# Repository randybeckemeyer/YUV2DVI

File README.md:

# YUV2DVI
Component Video to DVI for Capture Cards

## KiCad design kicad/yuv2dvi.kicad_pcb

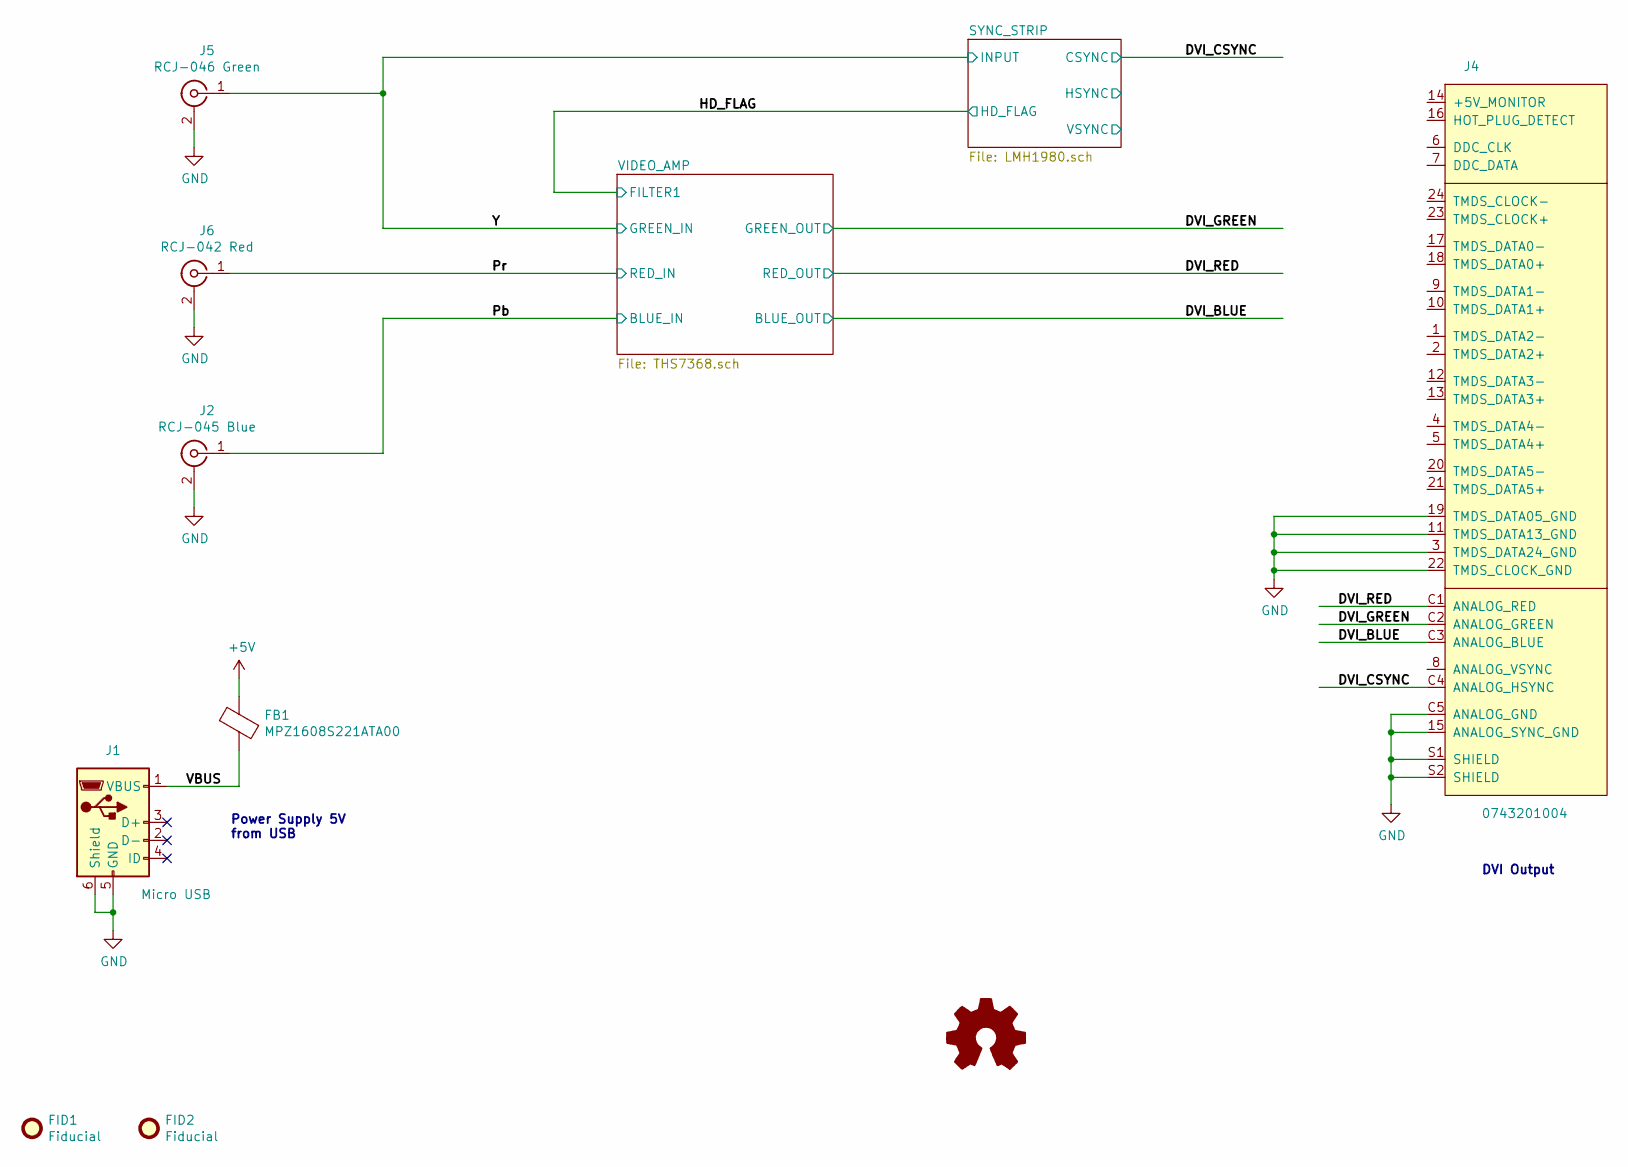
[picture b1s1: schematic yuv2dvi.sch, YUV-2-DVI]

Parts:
FB1: MPZ1608S221ATA00; L_0603_1608Metric_Pad1.05x0.95mm_HandSolder; MPN MPZ1608S221ATA00; Digikey 445-1565-1-ND
FID1, FID2: Fiducial; Fiducial_1mm_Mask2mm
J1: Micro USB; USB_Micro-B_Molex-105017-0001; MPN 1050170001; Digikey WM1399CT-ND
J2: RCJ-045 Blue; Connector-RCJ-045; MPN RCJ-045; Digikey CP-1422-ND
J4: 0743201004; Connector-DVI-0743201004; MPN 0743201004; Digikey WM5600-ND
J5: RCJ-046 Green; Connector-RCJ-046; MPN RCJ-046; Digikey CP-1423-ND
J6: RCJ-042 Red; Connector-RCJ-042; MPN RCJ-042; Digikey CP-1419-ND
LOGO1: Logo_Open_Hardware_Small; OSHW-Logo2_14.6x12mm_SilkScreen

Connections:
+5V: FB1.1; also elsewhere on the board
/DVI_BLUE: J4.C3 (ANALOG_BLUE); also elsewhere on the board
/DVI_CSYNC: J4.C4 (ANALOG_HSYNC); also elsewhere on the board
/DVI_GREEN: J4.C2 (ANALOG_GREEN); also elsewhere on the board
/DVI_RED: J4.C1 (ANALOG_RED); also elsewhere on the board
/Pb: J2.1 (In); also elsewhere on the board
/Pr: J6.1 (In); also elsewhere on the board
/VBUS: FB1.2, J1.1 (VBUS)
/Y: J5.1 (In); also elsewhere on the board
GND: J1.5 (GND), J1.6 (Shield), J2.2 (Ext), J4.3 (TMDS_DATA24_GND), J4.11 (TMDS_DATA13_GND), J4.15 (ANALOG_SYNC_GND), J4.19 (TMDS_DATA05_GND), J4.22 (TMDS_CLOCK_GND), J4.C5 (ANALOG_GND), J4.S1 (SHIELD), J4.S2 (SHIELD), J5.2 (Ext), J6.2 (Ext); also elsewhere on the board

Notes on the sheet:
Power Supply 5V from USB
DVI Output

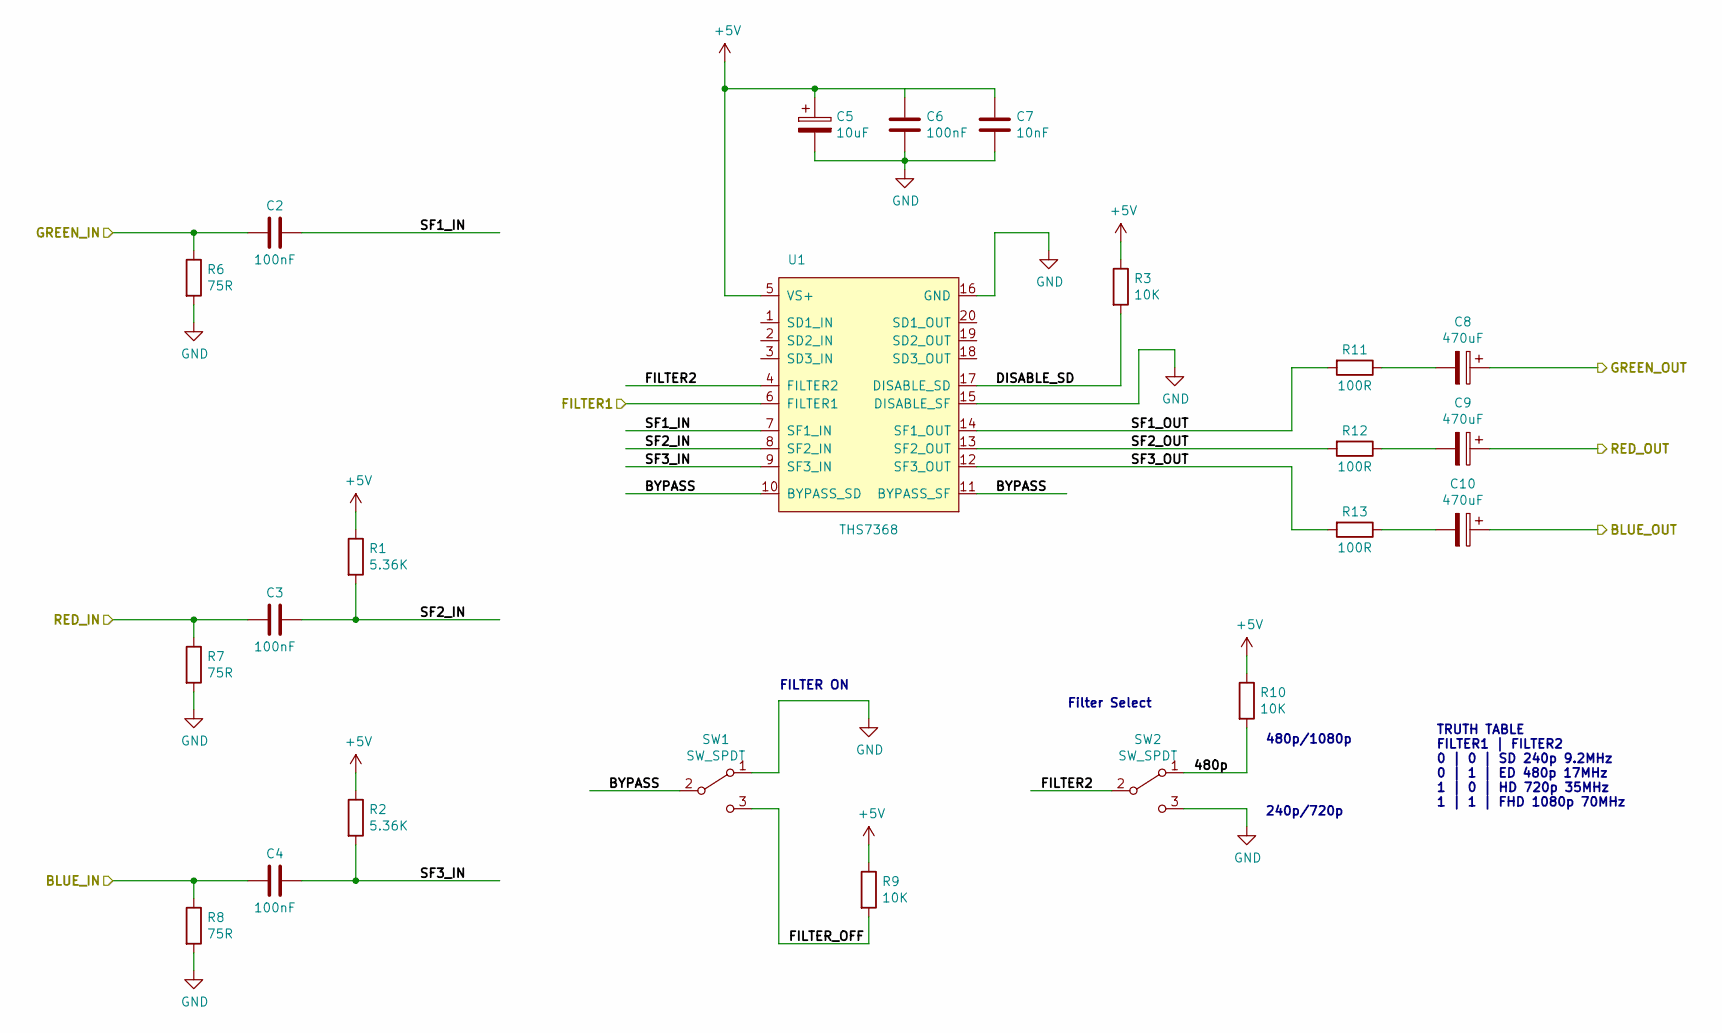
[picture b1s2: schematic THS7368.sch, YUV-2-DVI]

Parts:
C2, C3, C4, C6: 100nF; C_0603_1608Metric_Pad1.05x0.95mm_HandSolder; MPN CC0603KRX7R9BB104; Digikey 311-1344-1-ND
C5: 10uF; CP_EIA-3216-18_Kemet-A_Pad1.58x1.35mm_HandSolder; MPN TAJA106K016RNJ; Digikey 478-1655-1-ND
C7: 10nF; C_0603_1608Metric_Pad1.05x0.95mm_HandSolder; MPN CC0603KRX7R9BB103; Digikey 311-1085-1-ND
C8, C9, C10: 470uF; CP_Elec_8x10.5; MPN EEE-HA1A471UP; Digikey PCE4178CT-ND
R1, R2: 5.36K; R_0603_1608Metric_Pad1.05x0.95mm_HandSolder; MPN RC0603FR-075K36L; Digikey 311-5.36KHRCT-ND
R3, R9, R10: 10K; R_0603_1608Metric_Pad1.05x0.95mm_HandSolder; MPN RC0603FR-0710KL; Digikey 311-10.0KHRCT-ND
R6, R7, R8: 75R; R_0603_1608Metric_Pad1.05x0.95mm_HandSolder; MPN RC0603FR-0775RL; Digikey 311-75.0HRCT-ND
R11, R12, R13: 100R; R_0603_1608Metric_Pad1.05x0.95mm_HandSolder; MPN RC0603FR-07100RL; Digikey 311-100HRCT-ND
SW1, SW2: SW_SPDT; SW_NKK_GW12RCV; MPN GW12RCV; Digikey 360-3430-ND
U1: THS7368; TSSOP-20_4.4x6.5mm_P0.65mm; MPN THS7368IPWR; Digikey 296-25625-1-ND

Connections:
+5V: C5.1, C6.1, C7.1, R1.1, R2.1, R3.1, R9.1, R10.1, U1.5 (VS+); also elsewhere on the board
/DVI_BLUE: C10.1; also elsewhere on the board
/DVI_GREEN: C8.1; also elsewhere on the board
/DVI_RED: C9.1; also elsewhere on the board
/HD_FLAG: U1.6 (FILTER1); also elsewhere on the board
/Pb: C4.2, R8.1; also elsewhere on the board
/Pr: C3.2, R7.1; also elsewhere on the board
/VIDEO_AMP/480p: R10.2, SW2.1 (A)
/VIDEO_AMP/BYPASS: SW1.2 (B), U1.10 (BYPASS_SD), U1.11 (BYPASS_SF)
/VIDEO_AMP/DISABLE_SD: R3.2, U1.17 (DISABLE_SD)
/VIDEO_AMP/FILTER2: SW2.2 (B), U1.4 (FILTER2)
/VIDEO_AMP/FILTER_OFF: R9.2, SW1.3 (C)
/VIDEO_AMP/SF1_IN: C2.1, U1.7 (SF1_IN)
/VIDEO_AMP/SF1_OUT: R11.2, U1.14 (SF1_OUT)
/VIDEO_AMP/SF2_IN: C3.1, R1.2, U1.8 (SF2_IN)
/VIDEO_AMP/SF2_OUT: R12.2, U1.13 (SF2_OUT)
/VIDEO_AMP/SF3_IN: C4.1, R2.2, U1.9 (SF3_IN)
/VIDEO_AMP/SF3_OUT: R13.2, U1.12 (SF3_OUT)
/Y: C2.2, R6.1; also elsewhere on the board
GND: C5.2, C6.2, C7.2, R6.2, R7.2, R8.2, SW1.1 (A), SW2.3 (C), U1.15 (DISABLE_SF), U1.16 (GND); also elsewhere on the board
unnamed: C8.2, R11.1
unnamed: C9.2, R12.1
unnamed: C10.2, R13.1

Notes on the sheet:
FILTER ON
TRUTH TABLE FILTER1 | FILTER2 0 | 0 | SD 240p 9.2MHz 0 | 1 | ED 480p 17MHz 1 | 0 | HD 720p 35MHz 1 | 1 | FHD 1080p 70MHz
Filter Select
240p/720p
480p/1080p

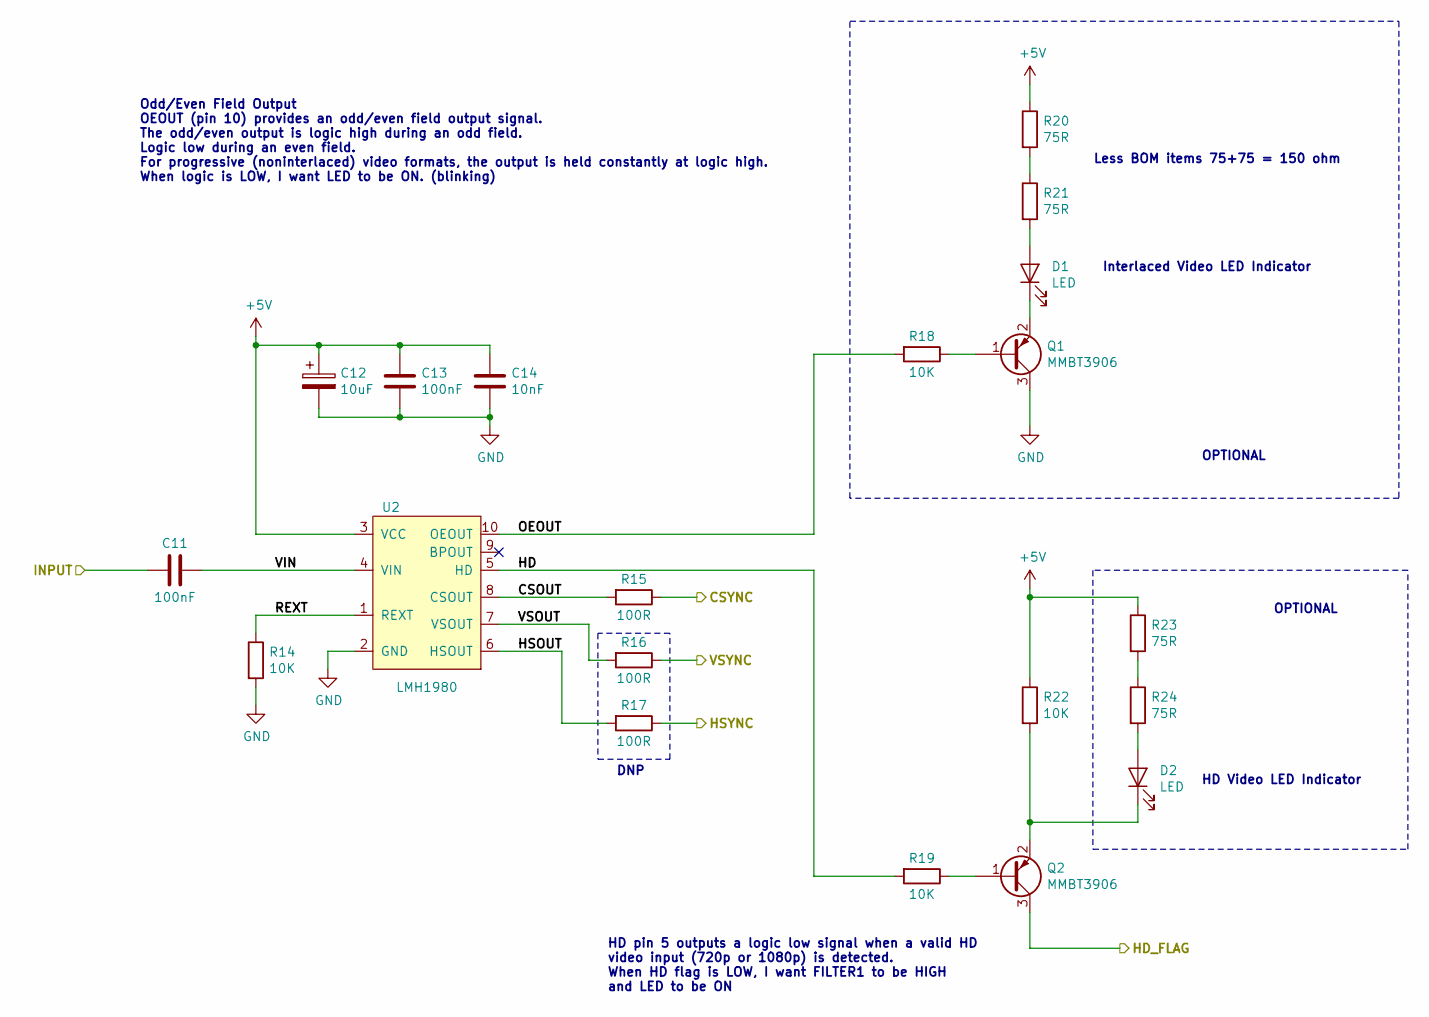
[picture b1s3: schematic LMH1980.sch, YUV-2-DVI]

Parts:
C11, C13: 100nF; C_0603_1608Metric_Pad1.05x0.95mm_HandSolder; MPN CC0603KRX7R9BB104; Digikey 311-1344-1-ND
C12: 10uF; CP_EIA-3216-18_Kemet-A_Pad1.58x1.35mm_HandSolder; MPN TAJA106K016RNJ; Digikey 478-1655-1-ND
C14: 10nF; C_0603_1608Metric_Pad1.05x0.95mm_HandSolder; MPN CC0603KRX7R9BB103; Digikey 311-1085-1-ND
D1, D2: LED; LED_0603_1608Metric_Pad1.05x0.95mm_HandSolder; MPN LTST-C190GKT; Digikey 160-1183-1-ND
Q1, Q2: MMBT3906; SOT-23; MPN MMBT3906LT1G; Digikey MMBT3906LT1GOSCT-ND
R14, R18, R19, R22: 10K; R_0603_1608Metric_Pad1.05x0.95mm_HandSolder; MPN RC0603FR-0710KL; Digikey 311-10.0KHRCT-ND
R15, R16, R17: 100R; R_0603_1608Metric_Pad1.05x0.95mm_HandSolder; MPN RC0603FR-07100RL; Digikey 311-100HRCT-ND
R20, R21, R23, R24: 75R; R_0603_1608Metric_Pad1.05x0.95mm_HandSolder; MPN RC0603FR-0775RL; Digikey 311-75.0HRCT-ND
U2: LMH1980; TSSOP-10_3x3mm_P0.5mm; MPN LMH1980MM/NOPB; Digikey LMH1980MM/NOPBCT-ND

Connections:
+5V: C12.1, C13.1, C14.1, R20.1, R22.1, R23.1, U2.3 (VCC); also elsewhere on the board
/DVI_CSYNC: R15.1; also elsewhere on the board
/HD_FLAG: Q2.3 (C); also elsewhere on the board
/SYNC_STRIP/CSOUT: R15.2, U2.8 (CSOUT)
/SYNC_STRIP/HD: R19.2, U2.5 (HD)
/SYNC_STRIP/HSOUT: R17.2, U2.6 (HSOUT)
/SYNC_STRIP/HSYNC: R17.1
/SYNC_STRIP/OEOUT: R18.2, U2.10 (OEOUT)
/SYNC_STRIP/REXT: R14.1, U2.1 (REXT)
/SYNC_STRIP/VIN: C11.1, U2.4 (VIN)
/SYNC_STRIP/VSOUT: R16.2, U2.7 (VSOUT)
/SYNC_STRIP/VSYNC: R16.1
/Y: C11.2; also elsewhere on the board
GND: C12.2, C13.2, C14.2, Q1.3 (C), R14.2, U2.2 (GND); also elsewhere on the board
unnamed: D1.1 (K), Q1.2 (E)
unnamed: D1.2 (A), R21.2
unnamed: D2.1 (K), Q2.2 (E), R22.2
unnamed: D2.2 (A), R24.2
unnamed: Q1.1 (B), R18.1
unnamed: Q2.1 (B), R19.1
unnamed: R20.2, R21.1
unnamed: R23.2, R24.1

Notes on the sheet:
HD pin 5 outputs a logic low signal when a valid HD video input (720p or 1080p) is detected. When HD flag is LOW, I want FILTER1 to be HIGH and LED to be ON
Odd/Even Field Output OEOUT (pin 10) provides an odd/even field output signal. The odd/even output is logic high during an odd field. Logic low during an even field. For progressive (noninterlaced) video formats, the output is held constantly at logic high. When logic is LOW, I want LED to be ON. (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
Interlaced Video LED Indicator
HD Video LED Indicator
Less BOM items 75+75 = 150 ohm
DNP
OPTIONAL

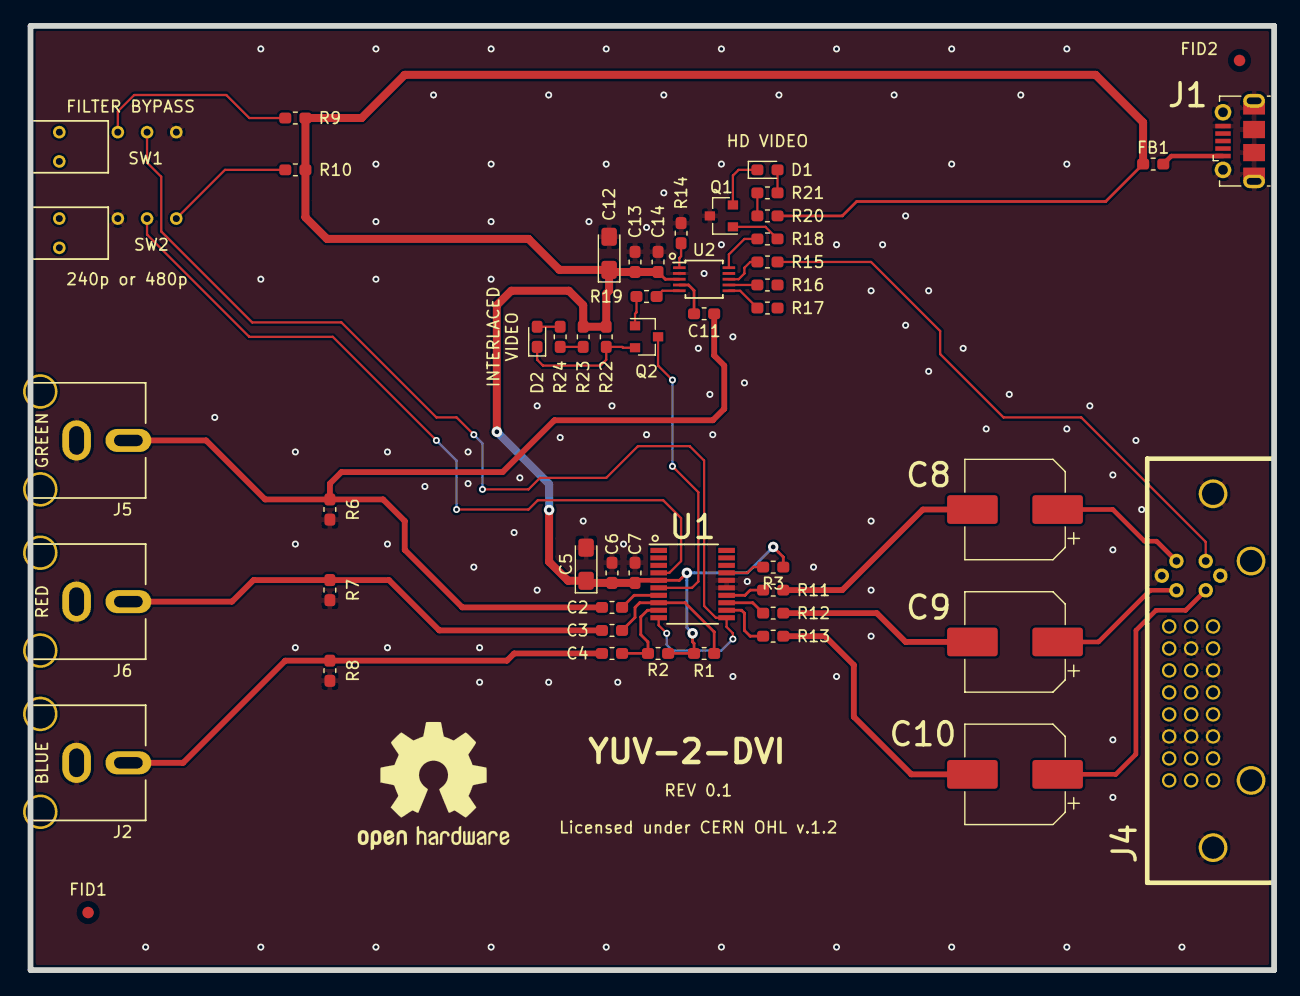
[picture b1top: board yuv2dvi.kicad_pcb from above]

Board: 2 copper layers, 108.0 x 82.0 mm, 52 parts (0 on the bottom side), 40 nets.

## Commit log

2019-03-24 move files into kicad folder

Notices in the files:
kicad/yuv2dvi.kicad_pcb:
Licensed under CERN OHL v.1.2
